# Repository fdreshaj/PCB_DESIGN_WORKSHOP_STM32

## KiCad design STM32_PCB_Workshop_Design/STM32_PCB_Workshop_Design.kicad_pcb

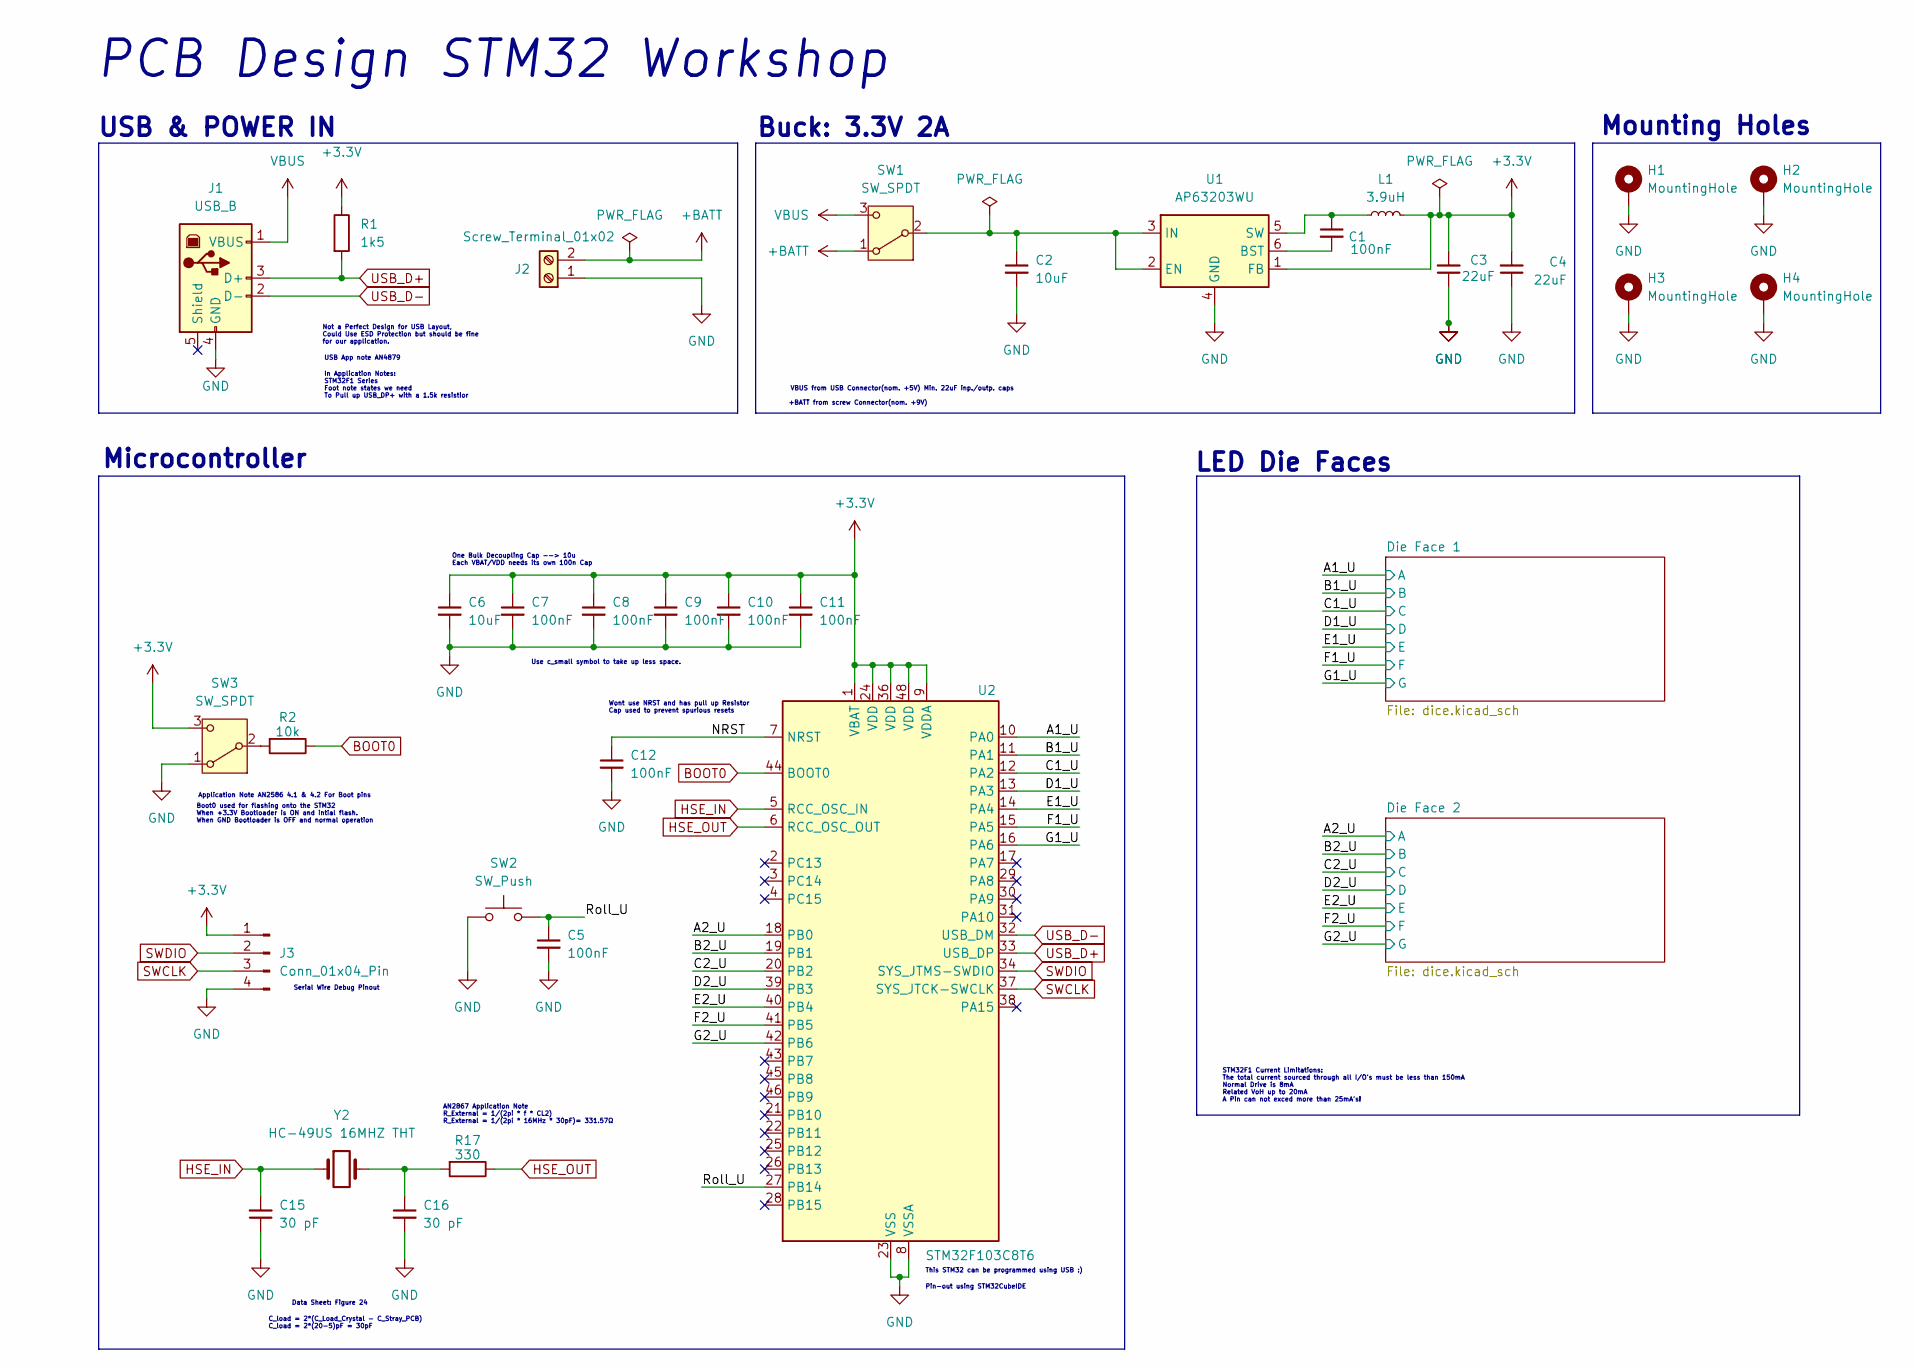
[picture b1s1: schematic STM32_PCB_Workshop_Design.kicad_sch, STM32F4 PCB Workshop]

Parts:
C1, C5, C7, C8, C9, C10, C11, C12: 100nF; C_1206_3216Metric_Pad1.33x1.80mm_HandSolder
C2, C6: 10uF; C_1206_3216Metric_Pad1.33x1.80mm_HandSolder
C3, C4: 22uF; C_1206_3216Metric_Pad1.33x1.80mm_HandSolder
C15, C16: 30 pF; C_1206_3216Metric_Pad1.33x1.80mm_HandSolder
H1, H2, H3, H4: MountingHole; MountingHole_3.2mm_M3_Pad
J1: USB_B; USB_B_OST_USB-B1HSxx_Horizontal
J2: Screw_Terminal_01x02; TerminalBlock_MaiXu_MX126-5.0-02P_1x02_P5.00mm
J3: Conn_01x04_Pin; PinHeader_1x04_P2.54mm_Vertical
L1: 3.9uH; L_Bourns_SDR0604
R1: 1k5; R_1206_3216Metric_Pad1.30x1.75mm_HandSolder
R2: 10k; R_1206_3216Metric_Pad1.30x1.75mm_HandSolder
R17: 330; R_1206_3216Metric_Pad1.30x1.75mm_HandSolder
SW1, SW3: SW_SPDT; SW_Slide_SPDT_Straight_CK_OS102011MS2Q
SW2: SW_Push; SW_SPST_Omron_B3F-40xx
U1: AP63203WU; TSOT-23-6
U2: STM32F103C8T6; LQFP-48_7x7mm_P0.5mm
Y2: HC-49US 16MHZ THT; Crystal_HC49-4H_Vertical

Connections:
+3.3V: C3.2, C4.2, C6.1, C7.1, C8.1, C9.1, C10.1, C11.1, J3.1, L1.2, R1.1, SW3.3 (C), U1.1 (FB), U2.1 (VBAT), U2.9 (VDDA), U2.24 (VDD), U2.36 (VDD), U2.48 (VDD)
+BATT: J2.2, SW1.1 (A)
/A1_U: U2.10 (PA0); also elsewhere on the board
/A2_U: U2.18 (PB0); also elsewhere on the board
/B1_U: U2.11 (PA1); also elsewhere on the board
/B2_U: U2.19 (PB1); also elsewhere on the board
/C1_U: U2.12 (PA2); also elsewhere on the board
/C2_U: U2.20 (PB2); also elsewhere on the board
/D1_U: U2.13 (PA3); also elsewhere on the board
/D2_U: U2.39 (PB3); also elsewhere on the board
/E1_U: U2.14 (PA4); also elsewhere on the board
/E2_U: U2.40 (PB4); also elsewhere on the board
/F1_U: U2.15 (PA5); also elsewhere on the board
/F2_U: U2.41 (PB5); also elsewhere on the board
/G1_U: U2.16 (PA6); also elsewhere on the board
/G2_U: U2.42 (PB6); also elsewhere on the board
/NRST: C12.1, U2.7 (NRST)
/Roll_U: C5.1, SW2.2, U2.27 (PB14)
BOOT0: R2.1, U2.44 (BOOT0)
GND: C2.2, C3.1, C4.1, C5.2, C6.2, C7.2, C8.2, C9.2, C10.2, C11.2, C12.2, C15.1, C16.2, H1.1, H2.1, H3.1, H4.1, J1.4 (GND), J2.1, J3.4, SW2.1, SW3.1 (A), U1.4 (GND), U2.8 (VSSA), U2.23 (VSS), U2.35 (VSS), U2.47 (VSS); also elsewhere on the board
HSE_IN: C15.2, U2.5 (PD0), Y2.1
HSE_OUT: R17.1, U2.6 (PD1)
unnamed: C16.1, R17.2, Y2.2
unnamed: C2.1, SW1.2 (B), U1.2 (EN), U1.3 (IN)
unnamed: R2.2, SW3.2 (B)
unnamed: C1.2, U1.6 (BST)
unnamed: C1.1, L1.1, U1.5 (SW)
SWCLK: J3.3, U2.37 (SYS_JTCK-SWCLK)
SWDIO: J3.2, U2.34 (SYS_JTMS-SWDIO)
USB_D+: J1.3 (D+), R1.2, U2.33 (USB_DP)
USB_D-: J1.2 (D-), U2.32 (USB_DM)
VBUS: J1.1 (VBUS), SW1.3 (C)

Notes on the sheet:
VBUS from USB Connector(nom. +5V) Min. 22uF inp./outp. caps
USB & POWER IN
PCB Design STM32 Workshop
USB App note AN4879
In Application Notes: STM32F1 Series Foot note states we need To Pull up USB_DP+ with a 1.5k resistior
This STM32 can be programmed using USB :)
+BATT from screw Connector(nom. +9V)
LED Die Faces
AN2867 Application Note R_External = 1/(2pi * f * CL2) R_External = 1/(2pi * 16MHz * 30pF)= 331.57Ω
C_load = 2*(C_Load_Crystal - C_Stray_PCB) C_load = 2*(20-5)pF = 30pF
Use c_small symbol to take up less space.
Mounting Holes
One Bulk Decoupling Cap --> 10u Each VBAT/VDD needs its own 100n Cap
Wont use NRST and has pull up Resistor Cap used to prevent spurious resets
Pin-out using STM32CubeIDE
Not a Perfect Design for USB Layout, Could Use ESD Protection but should be fine for our application.
Data Sheet: Figure 24
Buck: 3.3V 2A
Microcontroller
STM32F1 Current Limitations: The total current sourced through all I/O's must be less than 150mA Normal Drive is 8mA Related VoH up to 20mA A Pin can not exced more than 25mA's!
Boot0 used for flashing onto the STM32 When +3.3V Bootloader is ON and intial flash. When GND Bootloader is OFF and normal operation
Serial Wire Debug Pinout
Application Note AN2586 4.1 & 4.2 For Boot pins

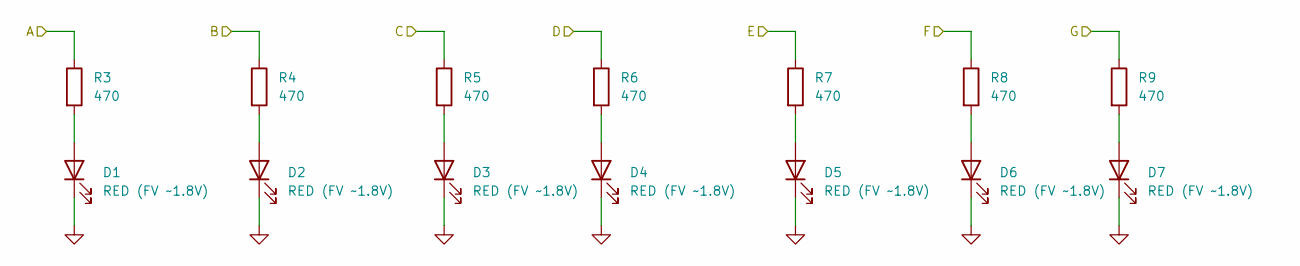
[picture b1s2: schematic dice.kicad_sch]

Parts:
D1, D2, D3, D4, D5, D6, D7: RED (FV ~1.8V); LED_D5.0mm
R3, R4, R5, R6, R7, R8, R9: 470; R_1206_3216Metric_Pad1.30x1.75mm_HandSolder

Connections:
/A1_U: R3.1; also elsewhere on the board
/B1_U: R4.1; also elsewhere on the board
/C1_U: R5.1; also elsewhere on the board
/D1_U: R6.1; also elsewhere on the board
/E1_U: R7.1; also elsewhere on the board
/F1_U: R8.1; also elsewhere on the board
/G1_U: R9.1; also elsewhere on the board
GND: D1.1 (K), D2.1 (K), D3.1 (K), D4.1 (K), D5.1 (K), D6.1 (K), D7.1 (K); also elsewhere on the board
unnamed: D1.2 (A), R3.2
unnamed: D2.2 (A), R4.2
unnamed: D3.2 (A), R5.2
unnamed: D4.2 (A), R6.2
unnamed: D5.2 (A), R7.2
unnamed: D6.2 (A), R8.2
unnamed: D7.2 (A), R9.2

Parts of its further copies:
D8, D9, D10, D11, D12, D13, D14: RED (FV ~1.8V); LED_D5.0mm
R10, R11, R12, R13, R14, R15, R16: 470; R_1206_3216Metric_Pad1.30x1.75mm_HandSolder

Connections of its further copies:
/A2_U: R10.1; also elsewhere on the board
/B2_U: R11.1; also elsewhere on the board
/C2_U: R12.1; also elsewhere on the board
/D2_U: R13.1; also elsewhere on the board
/E2_U: R14.1; also elsewhere on the board
/F2_U: R15.1; also elsewhere on the board
/G2_U: R16.1; also elsewhere on the board
GND: D8.1 (K), D9.1 (K), D10.1 (K), D11.1 (K), D12.1 (K), D13.1 (K), D14.1 (K); also elsewhere on the board
unnamed: D8.2 (A), R10.2
unnamed: D9.2 (A), R11.2
unnamed: D10.2 (A), R12.2
unnamed: D11.2 (A), R13.2
unnamed: D12.2 (A), R14.2
unnamed: D13.2 (A), R15.2
unnamed: D14.2 (A), R16.2

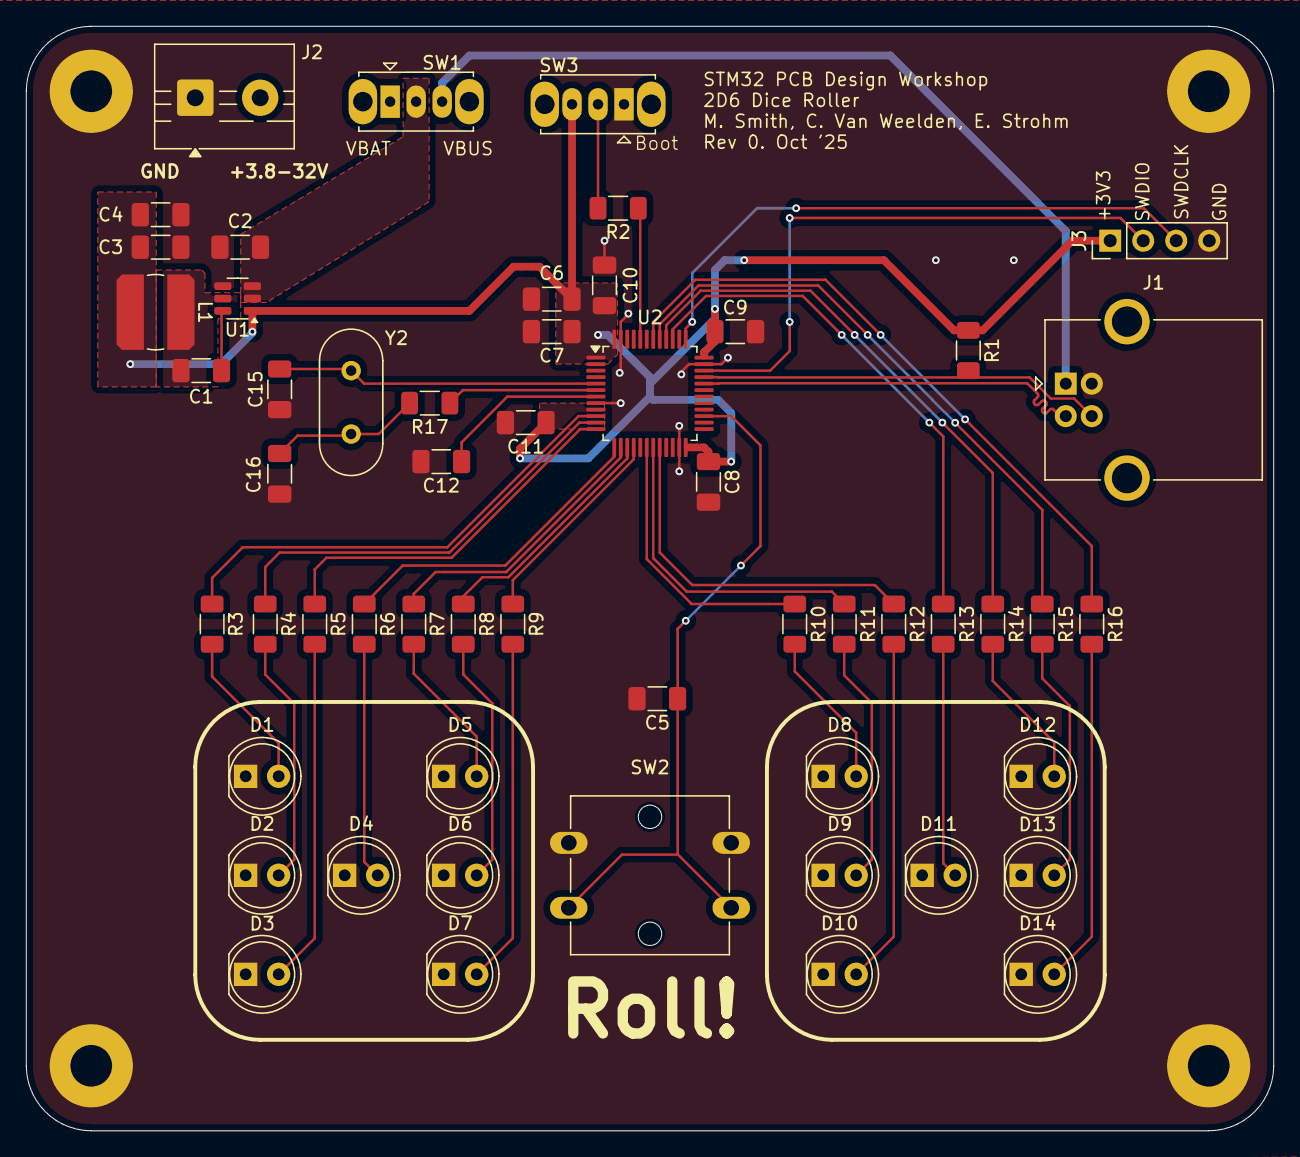
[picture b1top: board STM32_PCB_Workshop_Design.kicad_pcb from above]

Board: 2 copper layers, 96.0 x 85.0 mm, 59 parts (0 on the bottom side), 46 nets.

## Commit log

2025-10-19 Add STM32 and KiCad reference PDFs
    Added several application notes and datasheets for STM32 microcontrollers, as well as a KiCad cheatsheet, schematic, and layout PDFs to the repository for hardware and PCB design reference.
2025-10-19 minor changes
    minor changes
2025-10-22 Update on PDFS
    Update on PDFs
